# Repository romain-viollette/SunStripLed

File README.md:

SunStripLed
===========
dev contact: romain.viollette@gmail.com

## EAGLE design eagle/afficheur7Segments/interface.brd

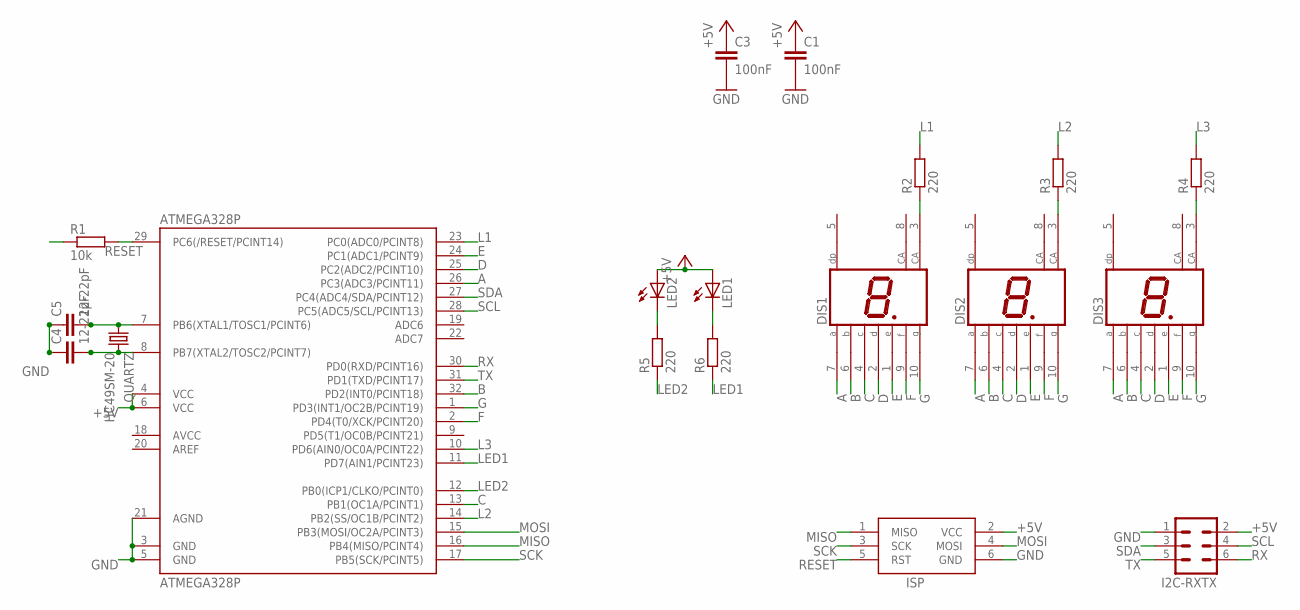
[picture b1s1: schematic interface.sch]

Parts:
ATMEGA328P: ATMEGA328P; TQFP32-08
C1, C3: 100nF; C0805
C4, C5: 12-22pF; C0805
DIS1, DIS2, DIS3: HD-H101; HDSP-M
I2C-RXTX: MA03-2
ISP: AVRISP-6; AVRISP
LED1, LED2: LED5MM
QUARTZ: HC49SM-20; HC49UP
R1: 10k; R0805
R2, R3, R4, R5, R6: 220; R0805

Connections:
+5V: ATMEGA328P.4 (VCC), ATMEGA328P.6 (VCC), C1.1, C3.1, I2C-RXTX.2, ISP.2 (VCC), LED1.A, LED2.A, R1.1
A: ATMEGA328P.26 (PC3(ADC3/PCINT11)), DIS1.7 (A), DIS2.7 (A), DIS3.7 (A)
B: ATMEGA328P.32 (PD2(INT0/PCINT18)), DIS1.6 (B), DIS2.6 (B), DIS3.6 (B)
C: ATMEGA328P.13 (PB1(OC1A/PCINT1)), DIS1.4 (C), DIS2.4 (C), DIS3.4 (C)
D: ATMEGA328P.25 (PC2(ADC2/PCINT10)), DIS1.2 (D), DIS2.2 (D), DIS3.2 (D)
E: ATMEGA328P.24 (PC1(ADC1/PCINT9)), DIS1.1 (E), DIS2.1 (E), DIS3.1 (E)
F: ATMEGA328P.2 (PD4(T0/XCK/PCINT20)), DIS1.9 (F), DIS2.9 (F), DIS3.9 (F)
G: ATMEGA328P.1 (PD3(INT1/OC2B/PCINT19)), DIS1.10 (G), DIS2.10 (G), DIS3.10 (G)
GND: ATMEGA328P.3 (GND), ATMEGA328P.5 (GND), ATMEGA328P.21 (AGND), C1.2, C3.2, C4.1, C5.1, I2C-RXTX.1, ISP.6 (GND)
L1: ATMEGA328P.23 (PC0(ADC0/PCINT8)), R2.2
L2: ATMEGA328P.14 (PB2(SS/OC1B/PCINT2)), R3.2
L3: ATMEGA328P.10 (PD6(AIN0/OC0A/PCINT22)), R4.2
LED1: ATMEGA328P.11 (PD7(AIN1/PCINT23)), R6.1
LED2: ATMEGA328P.12 (PB0(ICP1/CLKO/PCINT0)), R5.1
MISO: ATMEGA328P.16 (PB4(MISO/PCINT4)), ISP.1 (MISO)
MOSI: ATMEGA328P.15 (PB3(MOSI/OC2A/PCINT3)), ISP.4 (MOSI)
unnamed: ATMEGA328P.8 (PB7(XTAL2/TOSC2/PCINT7)), C4.2, QUARTZ.2
unnamed: ATMEGA328P.7 (PB6(XTAL1/TOSC1/PCINT6)), C5.2, QUARTZ.1
unnamed: DIS2.3 (CA), R3.1
unnamed: DIS3.3 (CA), R4.1
unnamed: LED2.K (C), R5.2
unnamed: DIS1.3 (CA), R2.1
unnamed: LED1.K (C), R6.2
RESET: ATMEGA328P.29 (PC6(/RESET/PCINT14)), ISP.5 (RST), R1.2
RX: ATMEGA328P.30 (PD0(RXD/PCINT16)), I2C-RXTX.6
SCK: ATMEGA328P.17 (PB5(SCK/PCINT5)), ISP.3 (SCK)
SCL: ATMEGA328P.28 (PC5(ADC5/SCL/PCINT13)), I2C-RXTX.4
SDA: ATMEGA328P.27 (PC4(ADC4/SDA/PCINT12)), I2C-RXTX.3
TX: ATMEGA328P.31 (PD1(TXD/PCINT17)), I2C-RXTX.5

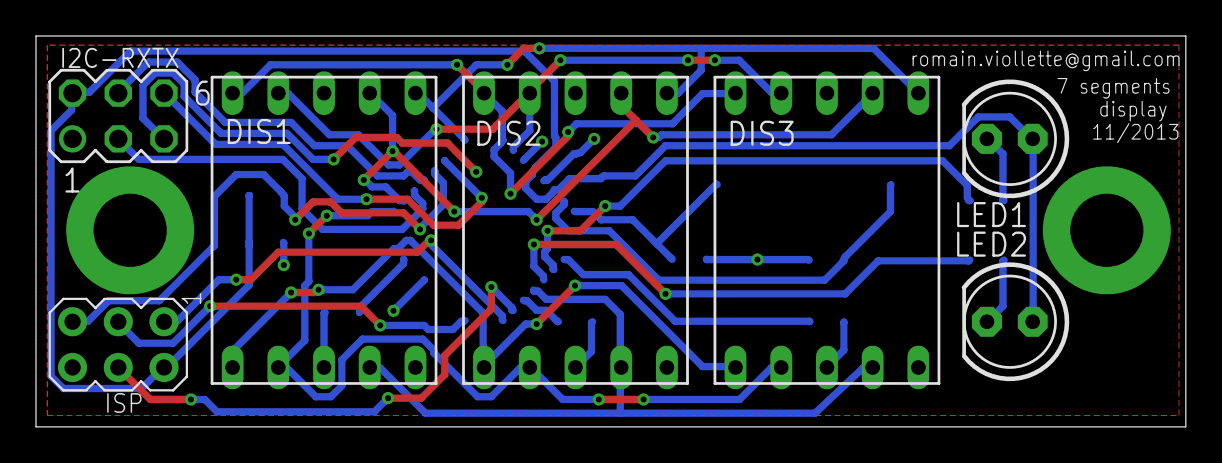
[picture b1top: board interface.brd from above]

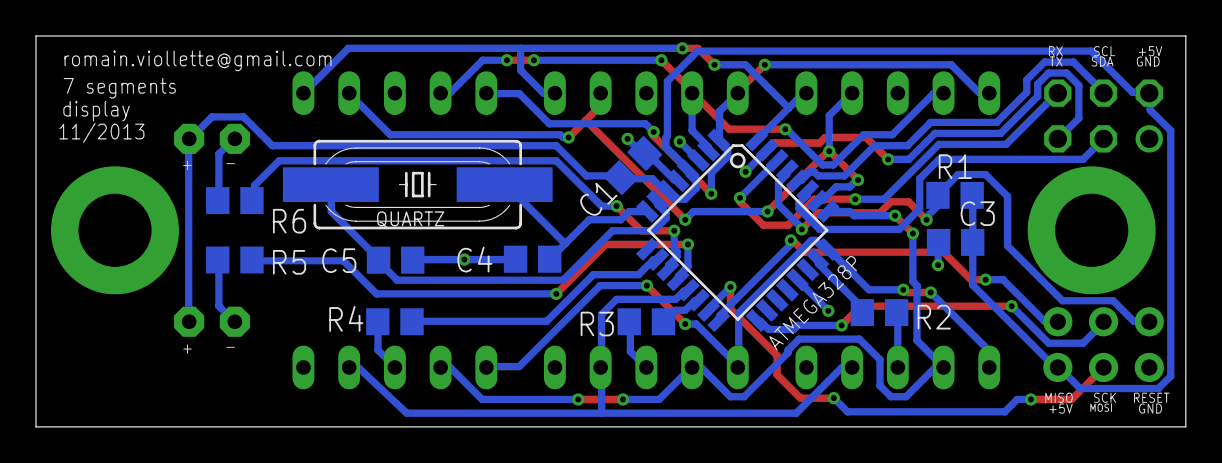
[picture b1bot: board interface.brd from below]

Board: 2 copper layers, 63.9 x 21.7 mm, 19 parts (12 on the bottom side), 29 nets.

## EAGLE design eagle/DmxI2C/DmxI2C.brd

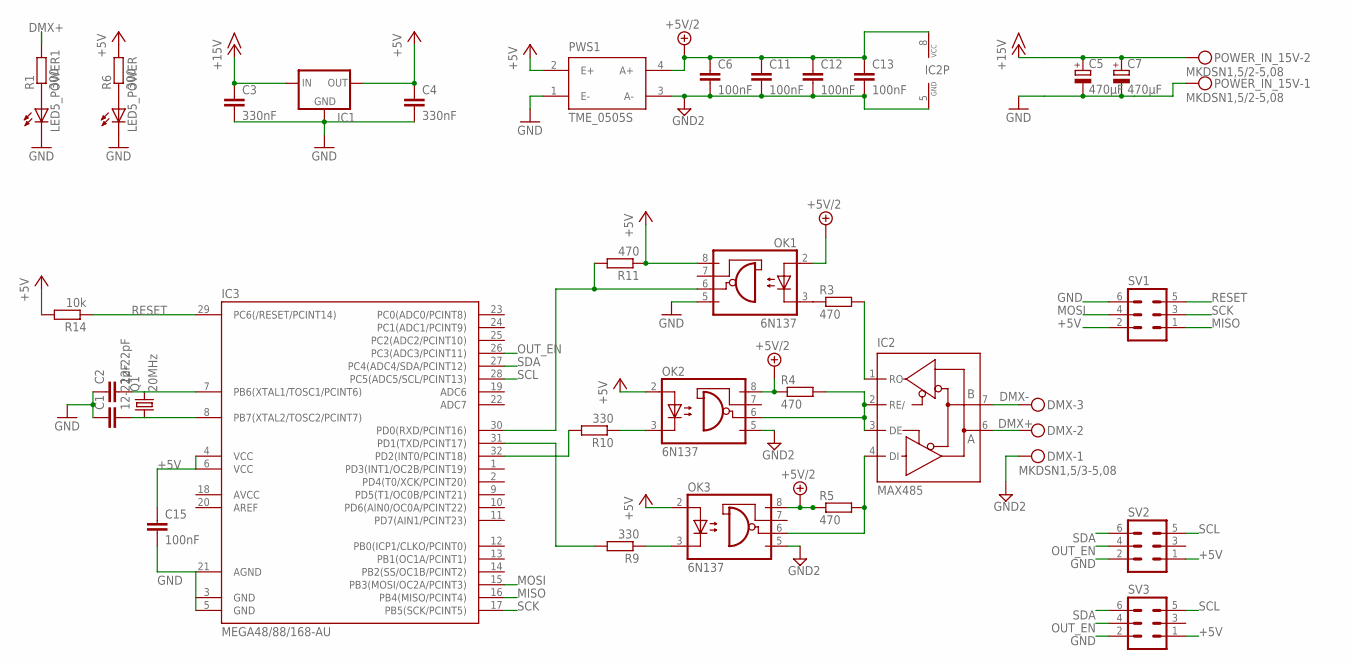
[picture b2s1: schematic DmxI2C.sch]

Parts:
C1, C2: 12-22pF; C0805
C3: 330nF; C0805
C4: 330nF; C050-025X075
C5, C7: 470µF; E2,5-6
C6, C11, C12, C13, C15: 100nF; C0805
DMX: MKDSN1,5/3-5,08
IC1: 78XXL
IC2: MAX485; DIL08; MPN MAX485
IC3: MEGA48/88/168-AU; TQFP32-08
LED5_POWER, LED5_POWER1: LED3MM
OK1, OK2, OK3: 6N137; DIL08
POWER_IN_15V: MKDSN1,5/2-5,08
PWS1: TME_0505S; TMEXXXXS
Q1: 20MHz; HC49UP
R1, R6: 300; R0805
R3, R4, R5, R11: 470; R0805
R9, R10: 330; R0805
R14: 10k; R0805
SV1, SV2, SV3: MA03-2

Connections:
+5V: C4.1, C15.1, IC1.OUT, IC3.4 (VCC), IC3.6 (VCC), OK1.8 (VCC), OK2.2 (A), OK3.2 (A), PWS1.2 (E+), R6.2, R11.1, R14.2, SV1.2, SV2.1, SV3.1
+5V/2: C6.1, C11.1, C12.1, C13.1, IC2.8 (VCC), OK1.2 (A), OK2.8 (VCC), OK3.8 (VCC), PWS1.4 (A+), R4.1, R5.1
+15V: C3.1, C5.+, C7.+, IC1.IN, POWER_IN_15V.2
DMX+: DMX.2, IC2.6 (A), R1.2
DMX-: DMX.3, IC2.7 (B)
GND: C1.1, C2.1, C3.2, C4.2, C5.-, C7.-, C15.2, IC1.GND, IC3.3 (GND), IC3.5 (GND), IC3.21 (AGND), LED5_POWER.K (C), LED5_POWER1.K (C), OK1.5 (GND), POWER_IN_15V.1, PWS1.1 (E-), SV1.6, SV2.2, SV3.2
GND2: C6.2, C11.2, C12.2, C13.2, DMX.1, IC2.5 (GND), OK2.5 (GND), OK3.5 (GND), PWS1.3 (A-)
MISO: IC3.16 (PB4(MISO/PCINT4)), SV1.1
MOSI: IC3.15 (PB3(MOSI/OC2A/PCINT3)), SV1.4
unnamed: OK1.3 (C), R3.1
unnamed: IC2.1 (RO), R3.2
unnamed: IC2.2 (RE/), IC2.3 (DE), OK2.6 (VO), R4.2
unnamed: IC2.4 (DI), OK3.6 (VO), R5.2
unnamed: OK3.3 (C), R9.1
unnamed: OK2.3 (C), R10.1
unnamed: IC3.30 (PD0(RXD/PCINT16)), OK1.6 (VO), R11.2
unnamed: IC3.32 (PD2(INT0/PCINT18)), R10.2
unnamed: C2.2, IC3.7 (PB6(XTAL1/TOSC1/PCINT6)), Q1.2
unnamed: LED5_POWER1.A, R1.1
unnamed: IC3.31 (PD1(TXD/PCINT17)), R9.2
unnamed: C1.2, IC3.8 (PB7(XTAL2/TOSC2/PCINT7)), Q1.1
unnamed: LED5_POWER.A, R6.1
OUT_EN: IC3.26 (PC3(ADC3/PCINT11)), SV2.4, SV3.4
RESET: IC3.29 (PC6(/RESET/PCINT14)), R14.1, SV1.5
SCK: IC3.17 (PB5(SCK/PCINT5)), SV1.3
SCL: IC3.28 (PC5(ADC5/SCL/PCINT13)), SV2.5, SV3.5
SDA: IC3.27 (PC4(ADC4/SDA/PCINT12)), SV2.6, SV3.6

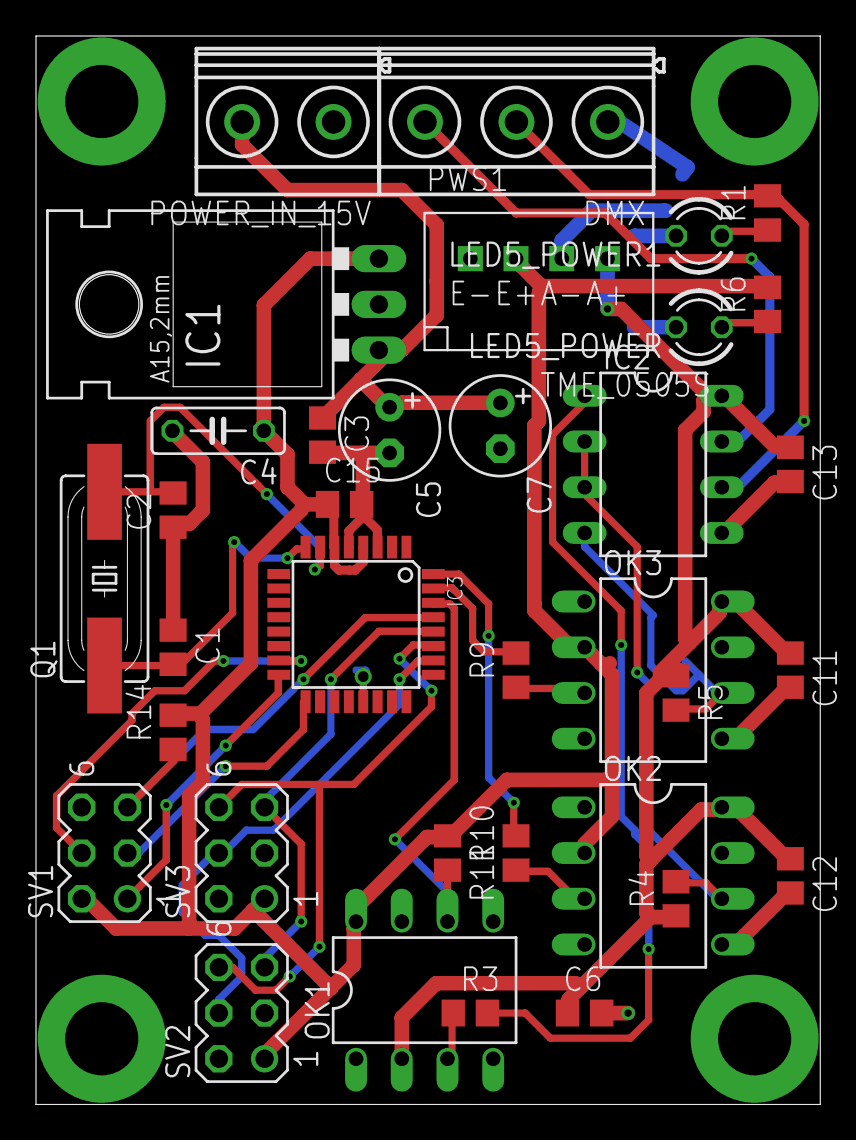
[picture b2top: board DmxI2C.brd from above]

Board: 2 copper layers, 43.6 x 59.4 mm, 35 parts (0 on the bottom side), 27 nets.

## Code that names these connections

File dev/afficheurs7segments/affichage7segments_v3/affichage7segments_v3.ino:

static const uint8_t PIN_L1 =   0; //PC0  //14
static const uint8_t PIN_L2 =   2; //PB2  //10
static const uint8_t PIN_L3 =   6; //PD6; //6
static const uint8_t PIN_A =    3; //PC3; //17
static const uint8_t PIN_B =    2; //PD2; //2
static const uint8_t PIN_C =    1; //PB1; //9
static const uint8_t PIN_D =    2; //PC2; //16
static const uint8_t PIN_E =    1; //PC1; //15
static const uint8_t PIN_F =    4; //PD4; //4
static const uint8_t PIN_G =    3; //PD3; //3
static const uint8_t PIN_LED1 = 7; //PD7; //7
static const uint8_t PIN_LED2 = 0; //PB0; //8

/*

 PORT B
 MSB                              LSB
 | 7 | 6 | 5 | 4 | 3 | 2  | 1 | 0   |
 | . | . | . | . | . | L2 | C | LED2|
 
 PORT C
 MSB                            LSB
 | 7 | 6 | 5 | 4 | 3 | 2 | 1 | 0  |
 | . | . | . | . | A | D | E | L1 |
 
 PORT D
 MSB                               LSB
 | 7    | 6  | 5 | 4 | 3 | 2 | 1 | 0 |
 | LED1 | L3 | . | F | G | B | . | . |
 
 
 SEVEN SEGMENT DISPLAYS:
 ___L1__       ___L2__       ___L3__ 
 |   A   |     |   A   |     |   A   |    displayValue[x] = 0ABCDEFG;
 |F     B|     |F     B|     |F     B|
 |   G   |     |   G   |     |   G   |
 |E     C|     |E     C|     |E     C|
 |___D___|     |___D___|     |___D___|
 
 
 */

static uint8_t A, B, C , D, E, F, G;    //Active High
static uint8_t L1, L2, L3, LED1, LED2;  //Active Low

static const uint8_t DDRB_ = (1<<PIN_L2) | (1<<PIN_C) | (1<<PIN_LED2);
static const uint8_t DDRC_ = (1<<PIN_A) | (1<<PIN_D) | (1<<PIN_E) | (1<<PIN_L1);
static const uint8_t DDRD_ = (1<<PIN_LED1) | (1<<PIN_L3) | (1<<PIN_F) | (1<<PIN_G) | (1<<PIN_B);

static uint8_t displayValue[3] = {0b01110111, 0b00011111, 0b01001110}; //text: AbC

static uint8_t segmentCounter = 0;

void setup()
{
  Serial.begin(9600);
  delay(1);
  Serial.println("\n-= Affichage 7 segments =-");

  A=B=C=D=E=F=G=0;
  L1=L2=L3=LED1=LED2=1;
  
  displayValue[0] = convertAscii2Segment('1');
  displayValue[1] = convertAscii2Segment('2');
  displayValue[2] = convertAscii2Segment('3');

  //settings pins as outputs:
  DDRB |= DDRB_;
  DDRC |= DDRC_;
  DDRD |= DDRD_;

  //initialize outputs:
  PORTB = (PORTB & ~DDRB_) | (L2<<PIN_L2) | (C<<PIN_C) | (LED2<<PIN_LED2);
  PORTC = (PORTC & ~DDRC_) | (A<<PIN_A) | (D<<PIN_D) | (E<<PIN_E) | (L1<<L1);
  PORTD = (PORTD & ~DDRD_) | (LED1<<PIN_LED1) | (L3<<PIN_L3) | (F<<PIN_F) | (G<<PIN_G) | (B<<PIN_B);

}

void loop()
{

  A= (segmentCounter==6)?LOW:HIGH;
  B= (segmentCounter==5)?LOW:HIGH;
  C= (segmentCounter==4)?LOW:HIGH;
  D= (segmentCounter==3)?LOW:HIGH;
  E= (segmentCounter==2)?LOW:HIGH;
  F= (segmentCounter==1)?LOW:HIGH;
  G= (segmentCounter==0)?LOW:HIGH;

  L1= (displayValue[0]&(1<<segmentCounter))?HIGH:LOW;
  L2= (displayValue[1]&(1<<segmentCounter))?HIGH:LOW;
  L3= (displayValue[2]&(1<<segmentCounter))?HIGH:LOW;

  //writting outputs:
  PORTB = (PORTB & ~DDRB_) | (L2<<PIN_L2) | (C<<PIN_C) | (LED2<<PIN_LED2);
  PORTC = (PORTC & ~DDRC_) | (A<<PIN_A) | (D<<PIN_D) | (E<<PIN_E) | (L1<<PIN_L1);
  PORTD = (PORTD & ~DDRD_) | (LED1<<PIN_LED1) | (L3<<PIN_L3) | (F<<PIN_F) | (G<<PIN_G) | (B<<PIN_B);

  segmentCounter++;
  if(segmentCounter >= 7)
    segmentCounter=0;

  delayMicroseconds(1000);
}



uint8_t convertAscii2Segment(char ascii)
{
  switch(ascii)
  {
    case '0' : return 0b01111110;
    case '1' : return 0b00110000;
    case '2' : return 0b01101101;
    case '3' : return 0b01111001;
    case '4' : return 0b00110011;
    case '5' : return 0b01011011;
    case '6' : return 0b01011111;
    case '7' : return 0b01110000;
    case '8' : return 0b01111111;
    case '9' : return 0b01110011;
    
    case 'a' :
    case 'A' : return 0b01110111;
    
    case 'b' :
    case 'B' : return 0b00011111;
    
    case 'c' : return 0b00001101;
    case 'C' : return 0b01001110;
    
    case 'd' :
    case 'D' : return 0b00111101;
    
    case 'e' :
    case 'E' : return 0b01001111;
    
    case 'f' :
    case 'F' : return 0b01000111;
    
    case 'g' :
    case 'G' : return 0b01011110;
    
    case 'h' : return 0b00010111;
    case 'H' : return 0b00110111;
    
    case 'i' :
    case 'I' : return 0b00000110;
    
    case 'j' :
    case 'J' : return 0b00111100;
    
    case 'k' :
    case 'K' : return 0b01010111;
    
    case 'l' : return 0b00000110;
    case 'L' : return 0b00001110;
    
    case 'm' :
    case 'M' : return 0b00111110;
    
    case 'n' :
    case 'N' : return 0b00111110;
    
    case 'o' : return 0b00011101;
    case 'O' : return 0b01111110;
    
    case 'p' :
    case 'P' : return 0b01100111;
    
    case 'q' :
    case 'Q' : return 0b01110011;
    
    case 'r' :
    case 'R' : return 0b00000101;
    
    case 's' :
    case 'S' : return 0b01011011;
    
    case 't' :
    case 'T' : return 0b00001111;
    
    case 'u' : return 0b00011100;
    case 'U' : return 0b00111110;
    
    case 'v' : return 0b00011100;
    case 'V' : return 0b00111110;
    
    case 'w' : return 0b00011100;
    case 'W' : return 0b00111110;
    
    case 'x' :
    case 'X' : return 0b00100101;
    
    case 'y' :
    case 'Y' : return 0b0111011;
    
    case 'z' :
    case 'Z' : return 0b01101100;
    

    case '-' : return 0b00000001;
    case '_' : return 0b00001000;
    case '=' : return 0b00001001;
    case '"' : return 0b00100010;
    case '\'': return 0b00100000;
    case '`' : return 0b00000010;
    case '.' : return 0b00010000;
    case ' ' : return 0b00000000;
    
    default:   return 0b00001000; //'_'
  } 
}

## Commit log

2013-11-20 cleanning
2013-11-20 clean
2013-11-20 routage
2014-03-25 I forgot about git syncing :/
